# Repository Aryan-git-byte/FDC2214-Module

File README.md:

# FDC2214R MODULE

It is a 4-channel capacitance sensing module designed on the FDC2214 IC by Texas Instrument.
This module can measure changes in capacitance using the onboard LC resonant sensors. it also provide four independant channels and can communicate with a MCU such as ESP32, Arduino etc over the standard I2C protocol.

# Specifications:
- resolution upto 28-bit
- 40 MHz of external clock
- 4 independent channels
- I2C address (0X2A DEFAULT, 0X2B CONFIGURABLE) 
- Operating temperature of -40°C to +125°C (IC0)

# What is it for?
It is for applications such as Proximity sensors, gesture recognition or level sensors for liquids.

# Schematic: 

The schematic of this module is very straight forward having the main FDC2214 IC, a 40 MHz external active oscillator, some passives and 2 connectors. 

The module also offer a jumper you can use to configure the I2C address of the Module. Which is 0X2A in default, and 0X2B after shifting the jumper.

# PCB:

This is the front view of the PCB, i have tried to route all the things on the first layer itself except for that jumper pad, which i had to put on the otherside, and is routed from the B.cu

This is the 3d view of the PCB, lookin neat :D

# How to Build?
I have provided all the required files needed to reproduce this board in this repo.
- Gerber files: [Here](production/gerber_to_order/FDC2214-Module_29.6x38.6mm_for_JLCPCB.zip)

Just go to any of your PCB manufacturer and upload this gerber file, after that order all the components listed in [here](production/BOM.csv). I will be using Digikey to order my components, If you are also using Digikey you can use this csv to import things in your cart - [cart](production/Digikey-cart.csv)

After getting both of the things, solder them onto their place and use it!

# Reference:
- FDC2214 datasheet - https://www.ti.com/lit/ds/symlink/fdc2112.pdf

# License:
This repo comes under the MIT license.

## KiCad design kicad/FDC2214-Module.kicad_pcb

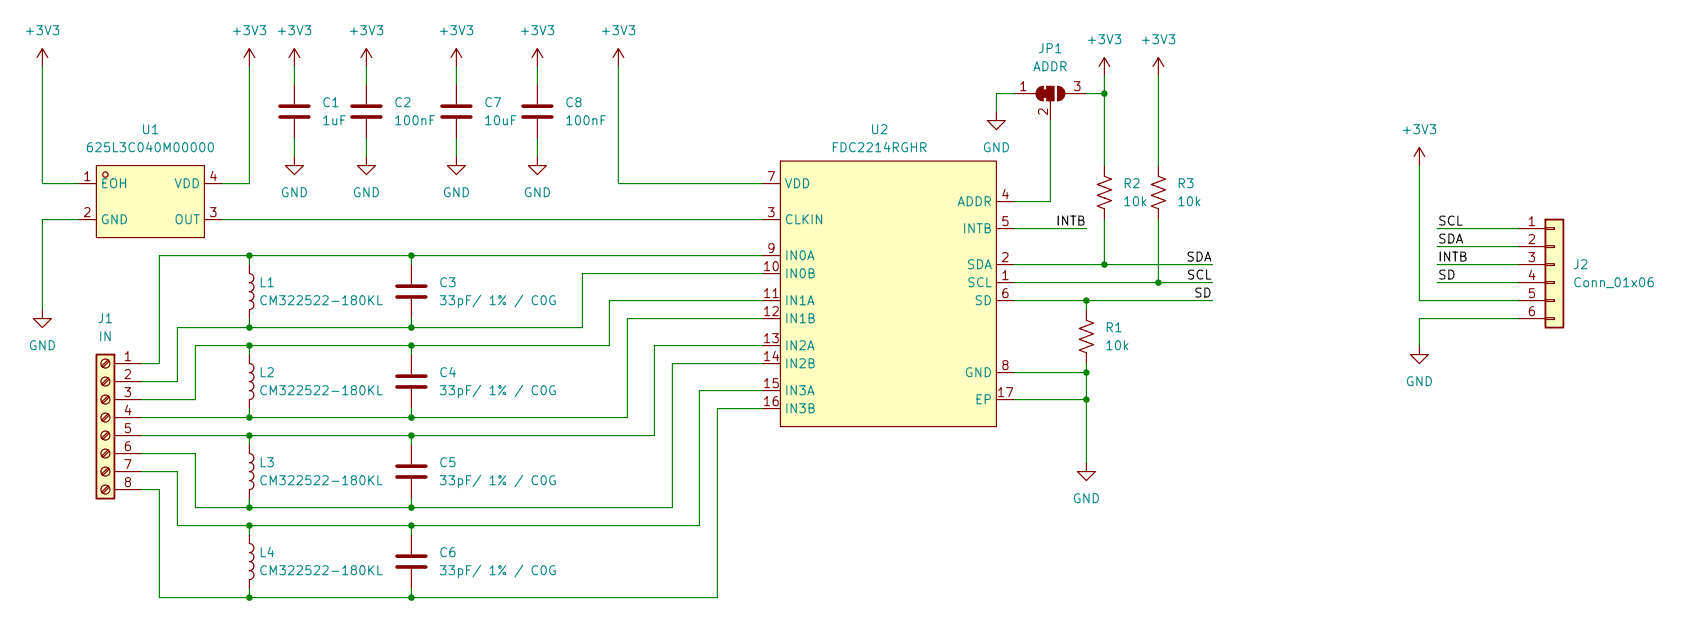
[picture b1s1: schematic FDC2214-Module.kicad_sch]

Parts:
C1: 1uF; C_0603_1608Metric
C2, C8: 100nF; C_0603_1608Metric
C3, C4, C5, C6: 33pF/ 1% / C0G; C_0603_1608Metric
C7: 10uF; C_0805_2012Metric
J1: IN; TerminalBlock_Phoenix_PT-1,5-8-3.5-H_1x08_P3.50mm_Horizontal
J2: Conn_01x06; JST_XH_S6B-XH-A_1x06_P2.50mm_Horizontal
JP1: ADDR; SolderJumper-3_P1.3mm_Bridged12_RoundedPad1.0x1.5mm
L1, L2, L3, L4: CM322522-180KL; L_1210_3225Metric_Pad1.42x2.65mm_HandSolder
R1, R2, R3: 10k; R_0603_1608Metric
U1: 625L3C040M00000; OSC-SMD_4P-L2.5-W2.0-BL
U2: FDC2214RGHR; WQFN-16_L4.0-W4.0-P0.50-BL-EP2.6

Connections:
+3V3: C1.1, C2.1, C7.1, C8.1, J2.5, JP1.3 (B), R2.1, R3.1, U1.1 (EOH), U1.4 (VDD), U2.7 (VDD)
/INTB: J2.3, U2.5 (INTB)
/SCL: J2.1, R3.2, U2.1 (SCL)
/SD: J2.4, R1.1, U2.6 (SD)
/SDA: J2.2, R2.2, U2.2 (SDA)
GND: C1.2, C2.2, C7.2, C8.2, J2.6, JP1.1 (A), R1.2, U1.2 (GND), U2.8 (GND), U2.17 (EP)
unnamed: C3.1, J1.1, L1.1, U2.9 (IN0A)
unnamed: C3.2, J1.2, L1.2, U2.10 (IN0B)
unnamed: C4.1, J1.3, L2.1, U2.11 (IN1A)
unnamed: C4.2, J1.4, L2.2, U2.12 (IN1B)
unnamed: C5.1, J1.5, L3.1, U2.13 (IN2A)
unnamed: C5.2, J1.6, L3.2, U2.14 (IN2B)
unnamed: C6.1, J1.7, L4.1, U2.15 (IN3A)
unnamed: C6.2, J1.8, L4.2, U2.16 (IN3B)
unnamed: JP1.2 (C), U2.4 (ADDR)
unnamed: U1.3 (OUT), U2.3 (CLKIN)

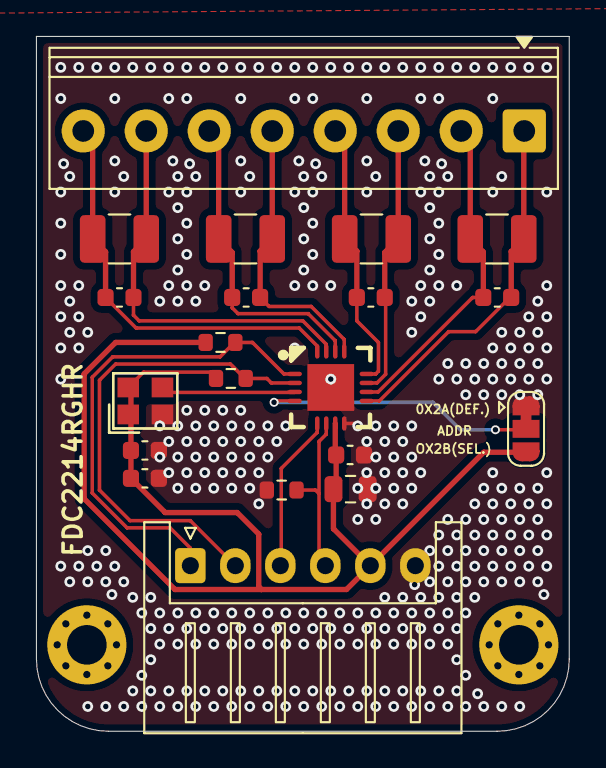
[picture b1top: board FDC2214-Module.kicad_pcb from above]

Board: 2 copper layers, 29.6 x 38.6 mm, 20 parts (0 on the bottom side), 16 nets.
